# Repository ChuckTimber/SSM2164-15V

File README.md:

# SSM2164-15V

[2164VCA - DIY Fx and Synthesizer](https://scrapbox.io/diyfx/2164VCA)

## 仕様
SSM2164によるVCAのテスト回路．
Expモードを2チャネル，Linモードを1チャネル

## 回路図

- [version 1.0](SSM2164-15V-Dual15V.pdf)

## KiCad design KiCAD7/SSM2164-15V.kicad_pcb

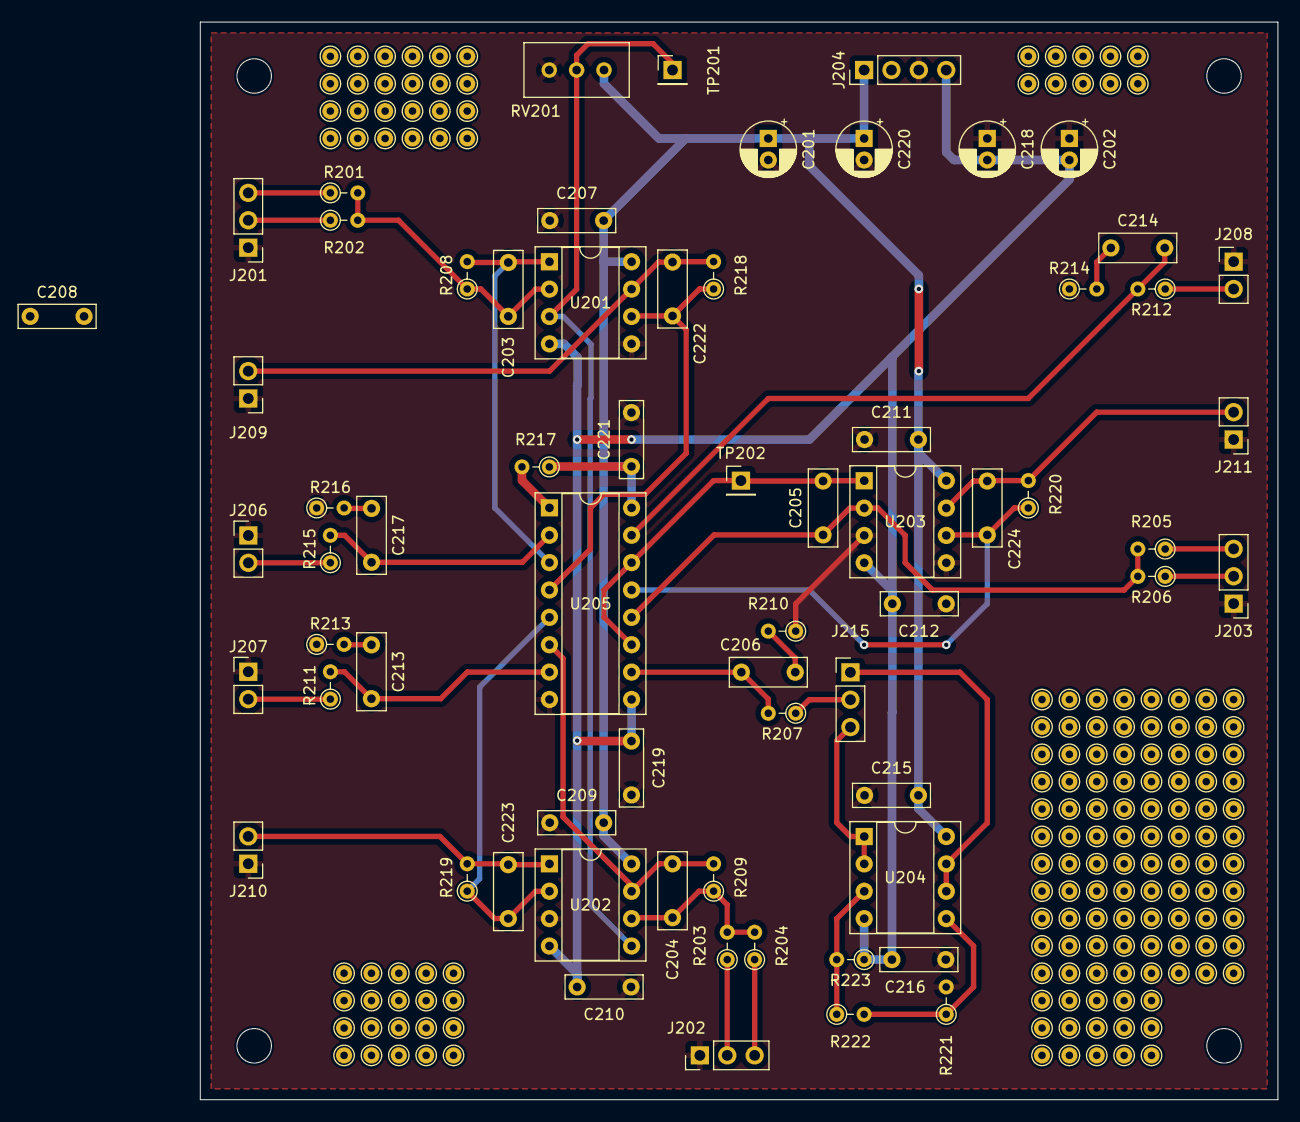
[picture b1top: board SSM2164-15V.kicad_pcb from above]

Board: 2 copper layers, 100.0 x 100.0 mm, 70 parts (0 on the bottom side), 39 nets.

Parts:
C201, C202, C218, C220: 10u; CP_Radial_D5.0mm_P2.00mm
C203, C204, C205, C222, C223, C224: 100p; C_Rect_L7.0mm_W2.5mm_P5.00mm
C206, C213, C214, C217: 560p; C_Rect_L7.0mm_W2.5mm_P5.00mm
C207, C208, C209, C210, C211, C212, C215, C216, C219, C221: 100n; C_Rect_L7.0mm_W2.0mm_P5.00mm
H101, H102, H103, H104: MountingHole; MountingHole_3.2mm_M3
J201: CV A; PinHeader_1x03_P2.54mm_Vertical
J202: CV B; PinHeader_1x03_P2.54mm_Vertical
J203, J215: CV C; PinHeader_1x03_P2.54mm_Vertical
J204: PWR; PinHeader_1x04_P2.54mm_Vertical
J206: VCA Input A; PinHeader_1x02_P2.54mm_Vertical
J207: VCA Input B; PinHeader_1x02_P2.54mm_Vertical
J208: VCA Input C; PinHeader_1x02_P2.54mm_Vertical
J209: VCA Output A; PinHeader_1x02_P2.54mm_Vertical
J210: VCA Output B; PinHeader_1x02_P2.54mm_Vertical
J211: VCA Output C; PinHeader_1x02_P2.54mm_Vertical
R201, R202, R203, R204, R205, R206, R207: 100k; R_Axial_DIN0204_L3.6mm_D1.6mm_P2.54mm_Vertical
R208, R209: 38k; R_Axial_DIN0204_L3.6mm_D1.6mm_P2.54mm_Vertical
R210, R213, R214, R216: 500; R_Axial_DIN0204_L3.6mm_D1.6mm_P2.54mm_Vertical
R211, R212, R215, R218, R219, R220: 30k; R_Axial_DIN0204_L3.6mm_D1.6mm_P2.54mm_Vertical
R217: 7k5; R_Axial_DIN0204_L3.6mm_D1.6mm_P2.54mm_Vertical
R221, R222, R223: 20k; R_Axial_DIN0204_L3.6mm_D1.6mm_P2.54mm_Vertical
RV201: 100k; Potentiometer_Bourns_3296W_Vertical
TP201: 1.4V; PinHeader_1x01_P2.54mm_Vertical
TP202: TestPoint; PinHeader_1x01_P2.54mm_Vertical
U201, U202, U203, U204: TL072; DIP-8_W7.62mm_Socket
U205: SSI2164; DIP-16_W7.62mm_Socket

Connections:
+15V: C201.1, C207.2, C209.2, C211.2, C215.2, C220.1, C221.1, J204.1, R217.1, RV201.3, U201.8 (V+), U202.8 (V+), U203.8 (V+), U204.8 (V+), U205.16 (V+)
-15V: C202.2, C208.2, C210.2, C212.2, C216.2, C218.2, C219.1, J204.4, R223.1, U201.4 (V-), U202.4 (V-), U203.4 (V-), U204.4 (V-), U205.9 (V-)
GND: C201.2, C202.1, C207.1, C208.1, C209.1, C210.1, C211.1, C212.1, C215.1, C216.1, C218.1, C219.2, C220.2, C221.2, J201.1, J202.1, J203.1, J204.3, J206.1, J207.1, J208.1, J209.1, J210.1, J211.1, R210.1, R213.1, R214.1, R216.1, R221.2, RV201.1, U201.5 (+), U202.3 (+), U203.3 (+), U203.5 (+), U205.8 (GND)
unnamed: C206.1, R210.2
unnamed: C213.1, R213.2
unnamed: C214.1, R214.2
unnamed: C217.1, R216.2
unnamed: J201.2, R202.1
unnamed: J201.3, R201.1
unnamed: J202.2, R204.1
unnamed: J202.3, R203.1
unnamed: J203.2, R206.1
unnamed: J203.3, R205.1
unnamed: J206.2, R215.1
unnamed: J207.2, R211.1
unnamed: J208.2, R212.1
unnamed: C222.2, J209.2, R218.2, U201.7
unnamed: C223.2, J210.2, R219.2, U202.1
unnamed: C224.2, J211.2, R220.2, U203.7
unnamed: RV201.2, TP201.1, U201.3 (+), U202.5 (+)
unnamed: C203.1, R201.2, R202.2, R208.1, U201.2 (-)
unnamed: C222.1, R218.1, U201.6 (-), U205.4 (I_OUT1)
unnamed: C223.1, R219.1, U202.2 (-), U205.5 (I_OUT2)
unnamed: C204.1, R203.2, R204.2, R209.1, U202.6 (-)
unnamed: C205.1, R205.2, R206.2, U203.2 (-), U205.12 (I_OUT3)
unnamed: C224.1, R220.1, U203.6 (-), U205.13 (I_OUT4)
unnamed: R222.1, R223.2, U204.3 (+)
unnamed: R221.1, R222.2, U204.5 (+)
unnamed: C217.2, R215.2, U205.2 (I_IN1)
unnamed: C213.2, R211.2, U205.7 (I_IN2)
unnamed: C206.2, R207.2, U205.10 (I_IN3)
unnamed: C214.2, R212.2, U205.15 (I_IN4)
unnamed: R217.2, U205.1 (MODE)
unnamed: C203.2, R208.2, U201.1, U205.3 (VC1)
unnamed: C204.2, R209.2, U202.7, U205.6 (VC2)
unnamed: C205.2, TP202.1, U203.1, U205.11 (VC3), U205.14 (VC4)
REF-5V: J215.1, U204.6 (-), U204.7
REF-10V: J215.3, U204.1, U204.2 (-)
REFV: J215.2, R207.1

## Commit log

2024-01-23 Added files
2024-01-23 Added
2024-01-23 Modified
